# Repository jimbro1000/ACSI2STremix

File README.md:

# ACSI2STreMix

This project is based on the ACSI2STM project by Jean-Matthieu
Coulon (retro16). https://github.com/retro16/acsi2stm

## Premise and Changes

The schematics for the project are unchanged from the original
(ignoring the addition of an additional 5V connection).

The changes are primarily to the PCB layout. Bulky components have
been moved to the rear of the board to permit extra clearance 
against the ST case.

Where feasible the board dimensions have been reduced.

All 0402 SMT components have been swapped for 0603 parts to ease
the job of hand soldering. For the same reason the clearance 
between parts has been increased.

The DB19 footprint has been reimplemented to correctly align the
pins and to use individual 1mm diameter board pins (such as these: 
https://www.aliexpress.com/item/4001366384308.html). This requires 
careful alignment of the pins during assembly - I strongly 
recommend using a spare, unpopulated PCB as a jig.

The USB power connection has been moved from the right, to the
left (as viewed from the computer) to bring the connection
closer to the cartridge port for those using a SidecarT.

## Build and Programming

The build of the board should now be easier and there is no 
particular build sequence needed if you are hand soldering
the board. It is probably worth leaving the DB19 pins until
last though to avoid bending them.

The firmware for programming the STM microcontroller should
be taken from the original acsi2stm github repository, no
changes should be required as of version 5.0d (November 2024).
All of the documentation in that repository should be
applicable here too.

## Credits

Thanks to

* Jean-Matthieu for creating the ACSI2STM project
* Glenn (CRG) for prompting this with his video on building the
original retro16 version
* Lee (MFMI) for providing entertainment and support
* The rest of the board folk team for just being brilliant

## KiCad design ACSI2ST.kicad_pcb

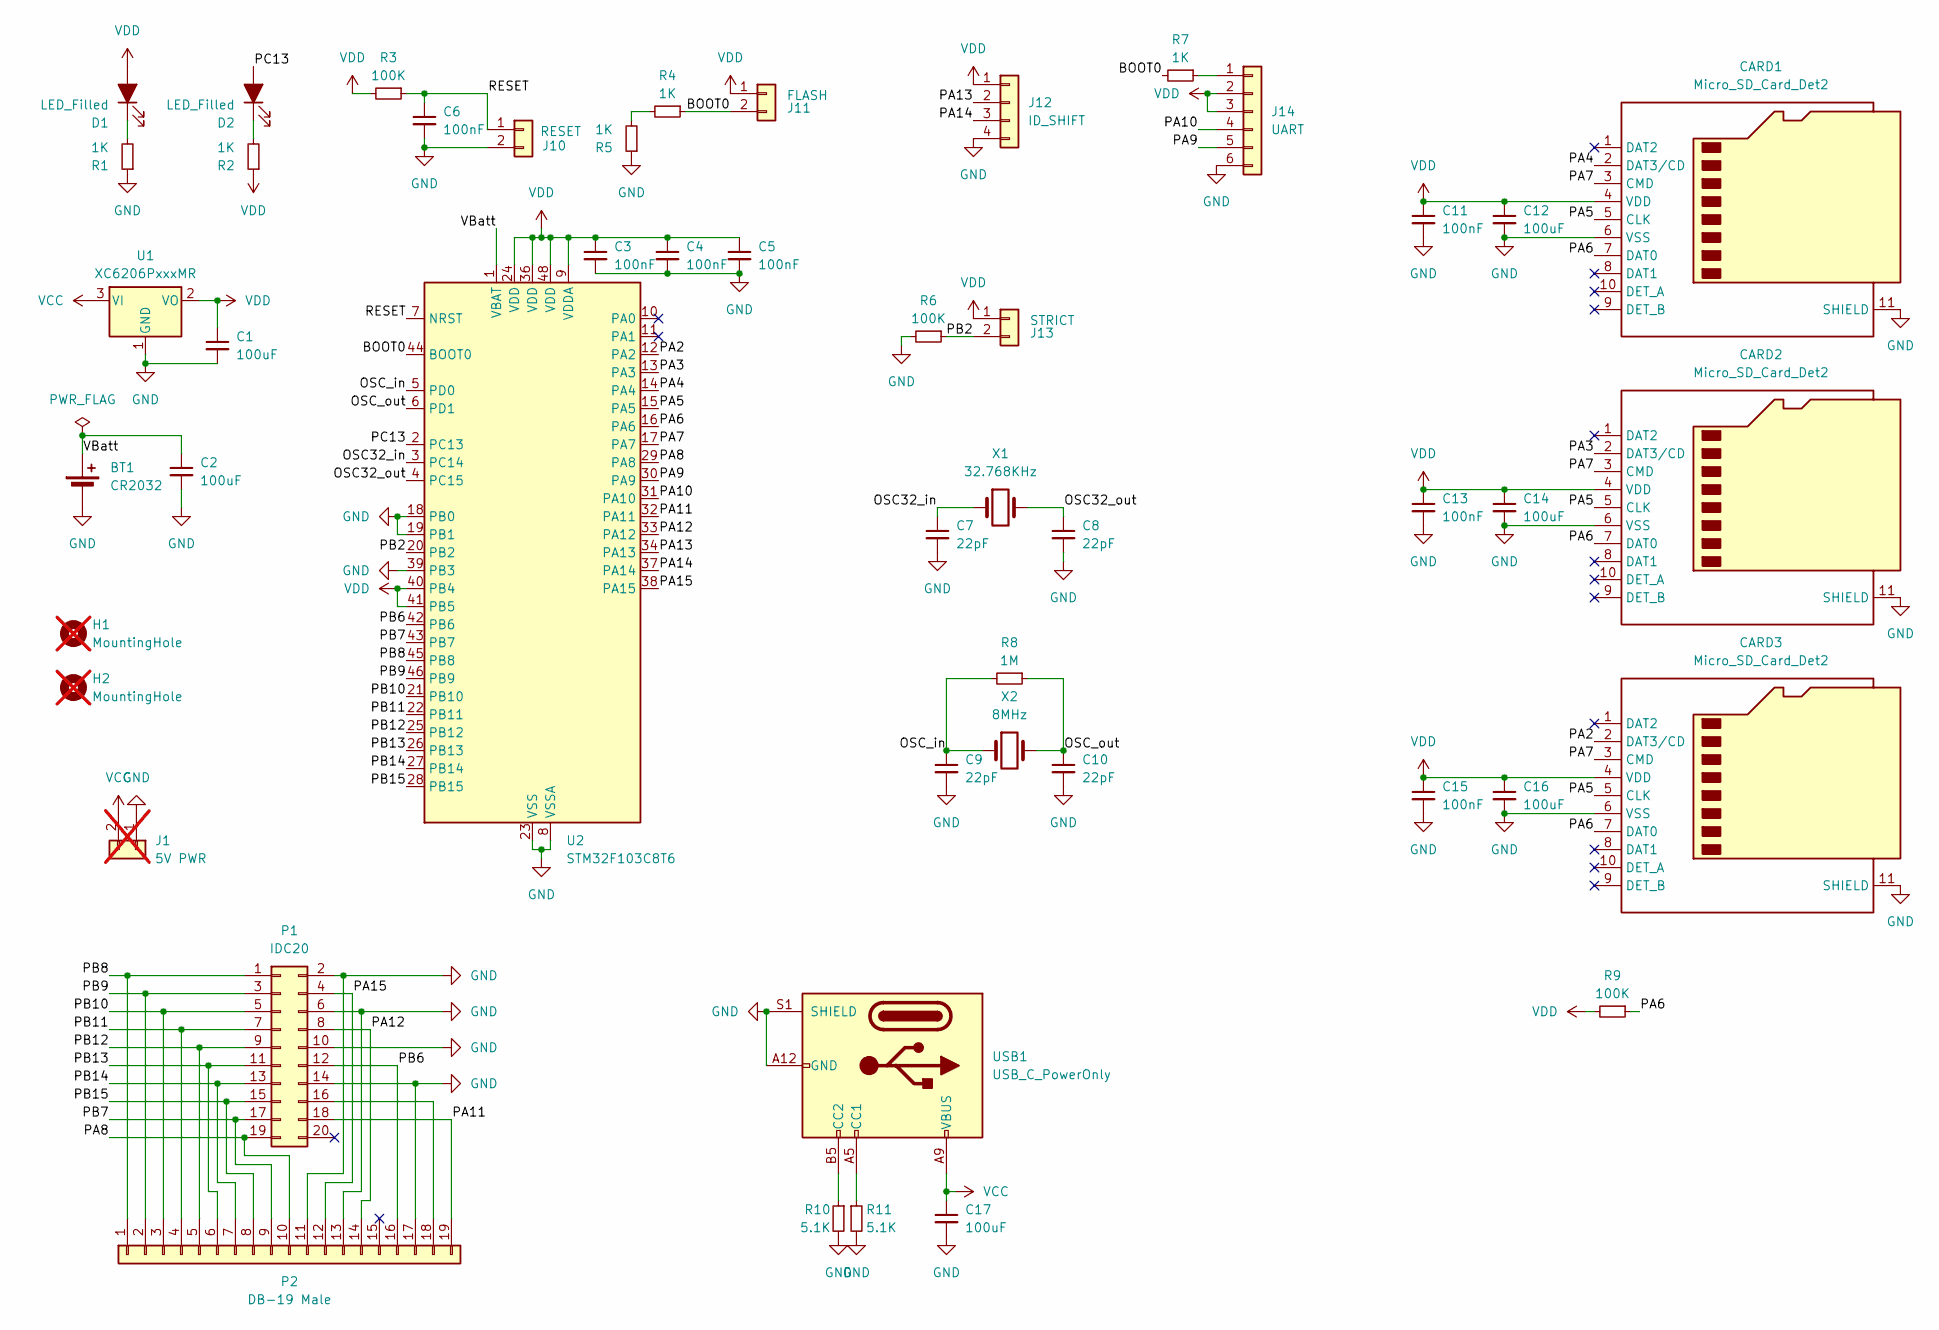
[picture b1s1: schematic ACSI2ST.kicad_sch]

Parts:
BT1: CR2032; BatteryHolder_Keystone_1060_1x2032; LCSC C238069
C1, C2, C12, C14, C16, C17: 100uF; C_1206_3216Metric; LCSC C15008
C3, C4, C5, C6, C11, C13, C15: 100nF; C_0603_1608Metric; LCSC C66501
C7, C8, C9, C10: 22pF; C_0603_1608Metric; LCSC C1653
CARD1, CARD2, CARD3: Micro_SD_Card_Det2; microSD_HC_Hirose_DM3BT-DSF-PEJS; DigiKey HR1942CT-ND
D1, D2: LED_Filled; LED_0805_2012Metric; LCSC C84256
H1, H2: MountingHole; MountingHole_2.5mm; not fitted
J1: 5V PWR; PinHeader_1x02_P2.54mm_Vertical; not fitted
J10: RESET; PinHeader_1x02_P2.54mm_Vertical; LCSC C124375
J11: FLASH; PinHeader_1x02_P2.54mm_Vertical; LCSC C124375
J12: ID_SHIFT; PinHeader_1x04_P2.54mm_Vertical; LCSC C124378
J13: STRICT; PinHeader_1x02_P2.54mm_Vertical; LCSC C124375
J14: UART; PinHeader_1x06_P2.54mm_Vertical; LCSC C40877
P1: IDC20; IDC-Header_2x10_P2.54mm_Vertical; LCSC C3405
P2: DB-19 Male; DSUB-19_Pins_Vertical
R1, R2, R4, R5, R7: 1K; R_0603_1608Metric; LCSC C2074292
R3, R6, R9: 100K; R_0603_1608Metric; LCSC C2087858
R8: 1M; R_0603_1608Metric; LCSC C2073548
R10, R11: 5.1K; R_0603_1608Metric; LCSC C1728901
U1: XC6206PxxxMR; SOT-23-3; LCSC C5446
U2: STM32F103C8T6; LQFP-48_7x7mm_P0.5mm; LCSC C8734
USB1: USB_C_PowerOnly; USB_C_Receptacle_GCT_USB4135-GF-A_6P_TopMnt_Horizontal; DigiKey 2073-USB4135-GF-ACT-ND
X1: 32.768KHz; Crystal_SMD_3215-2Pin_3.2x1.5mm; LCSC C32346
X2: 8MHz; Crystal_SMD_5032-2Pin_5.0x3.2mm; LCSC C115962

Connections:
/BOOT0: J11.2, R4.1, R7.2, U2.44 (BOOT0)
/OSC32_in: C7.1, U2.3 (PC14), X1.1
/OSC32_out: C8.1, U2.4 (PC15), X1.2
/OSC_in: C9.1, R8.2, U2.5 (PD0), X2.1
/OSC_out: C10.1, R8.1, U2.6 (PD1), X2.2
/PA2: CARD3.2 (DAT3/CD), U2.12 (PA2)
/PA3: CARD2.2 (DAT3/CD), U2.13 (PA3)
/PA4: CARD1.2 (DAT3/CD), U2.14 (PA4)
/PA5: CARD1.5 (CLK), CARD2.5 (CLK), CARD3.5 (CLK), U2.15 (PA5)
/PA6: CARD1.7 (DAT0), CARD2.7 (DAT0), CARD3.7 (DAT0), R9.1, U2.16 (PA6)
/PA7: CARD1.3 (CMD), CARD2.3 (CMD), CARD3.3 (CMD), U2.17 (PA7)
/PA8: P1.19, P2.10, U2.29 (PA8)
/PA9: J14.5, U2.30 (PA9)
/PA10: J14.4, U2.31 (PA10)
/PA11: P1.18, P2.19, U2.32 (PA11)
/PA12: P1.8, P2.14, U2.33 (PA12)
/PA13: J12.2, U2.34 (PA13)
/PA14: J12.3, U2.37 (PA14)
/PA15: P1.4, P2.12, U2.38 (PA15)
/PB2: J13.2, R6.1, U2.20 (PB2)
/PB6: P1.12, P2.16, U2.42 (PB6)
/PB7: P1.17, P2.9, U2.43 (PB7)
/PB8: P1.1, P2.1, U2.45 (PB8)
/PB9: P1.3, P2.2, U2.46 (PB9)
/PB10: P1.5, P2.3, U2.21 (PB10)
/PB11: P1.7, P2.4, U2.22 (PB11)
/PB12: P1.9, P2.5, U2.25 (PB12)
/PB13: P1.11, P2.6, U2.26 (PB13)
/PB14: P1.13, P2.7, U2.27 (PB14)
/PB15: P1.15, P2.8, U2.28 (PB15)
/PC13: D2.2 (A), U2.2 (PC13)
/RESET: C6.1, J10.1, R3.1, U2.7 (NRST)
/VBatt: BT1.1 (+), C2.1, U2.1 (VBAT)
GND: BT1.2 (-), C1.2, C2.2, C3.2, C4.2, C5.2, C6.2, C7.2, C8.2, C9.2, C10.2, C11.2, C12.2, C13.2, C14.2, C15.2, C16.2, C17.2, CARD1.6 (VSS), CARD1.11 (SHIELD), CARD2.6 (VSS), CARD2.11 (SHIELD), CARD3.6 (VSS), CARD3.11 (SHIELD), J1.1, J10.2, J12.4, J14.6, P1.2, P1.6, P1.10, P1.14, P2.11, P2.13, P2.17, R1.1, R5.1, R6.2, R10.2, R11.2, U1.1 (GND), U2.8 (VSSA), U2.18 (PB0), U2.19 (PB1), U2.23 (VSS), U2.35 (VSS), U2.39 (PB3), U2.47 (VSS), USB1.A12 (GND), USB1.B12 (GND), USB1.S1 (SHIELD)
unnamed: D1.1 (K), R1.2
unnamed: D2.1 (K), R2.2
unnamed: J14.1, R7.1
unnamed: P1.16, P2.18
unnamed: R4.2, R5.2
unnamed: R11.1, USB1.A5 (CC1)
unnamed: R10.1, USB1.B5 (CC2)
VCC: C17.1, J1.2, U1.3 (VI), USB1.A9 (VBUS), USB1.B9 (VBUS)
VDD: C1.1, C3.1, C4.1, C5.1, C11.1, C12.1, C13.1, C14.1, C15.1, C16.1, CARD1.4 (VDD), CARD2.4 (VDD), CARD3.4 (VDD), D1.2 (A), J11.1, J12.1, J13.1, J14.2, J14.3, R2.1, R3.2, R9.2, U1.2 (VO), U2.9 (VDDA), U2.24 (VDD), U2.36 (VDD), U2.40 (PB4), U2.41 (PB5), U2.48 (VDD)

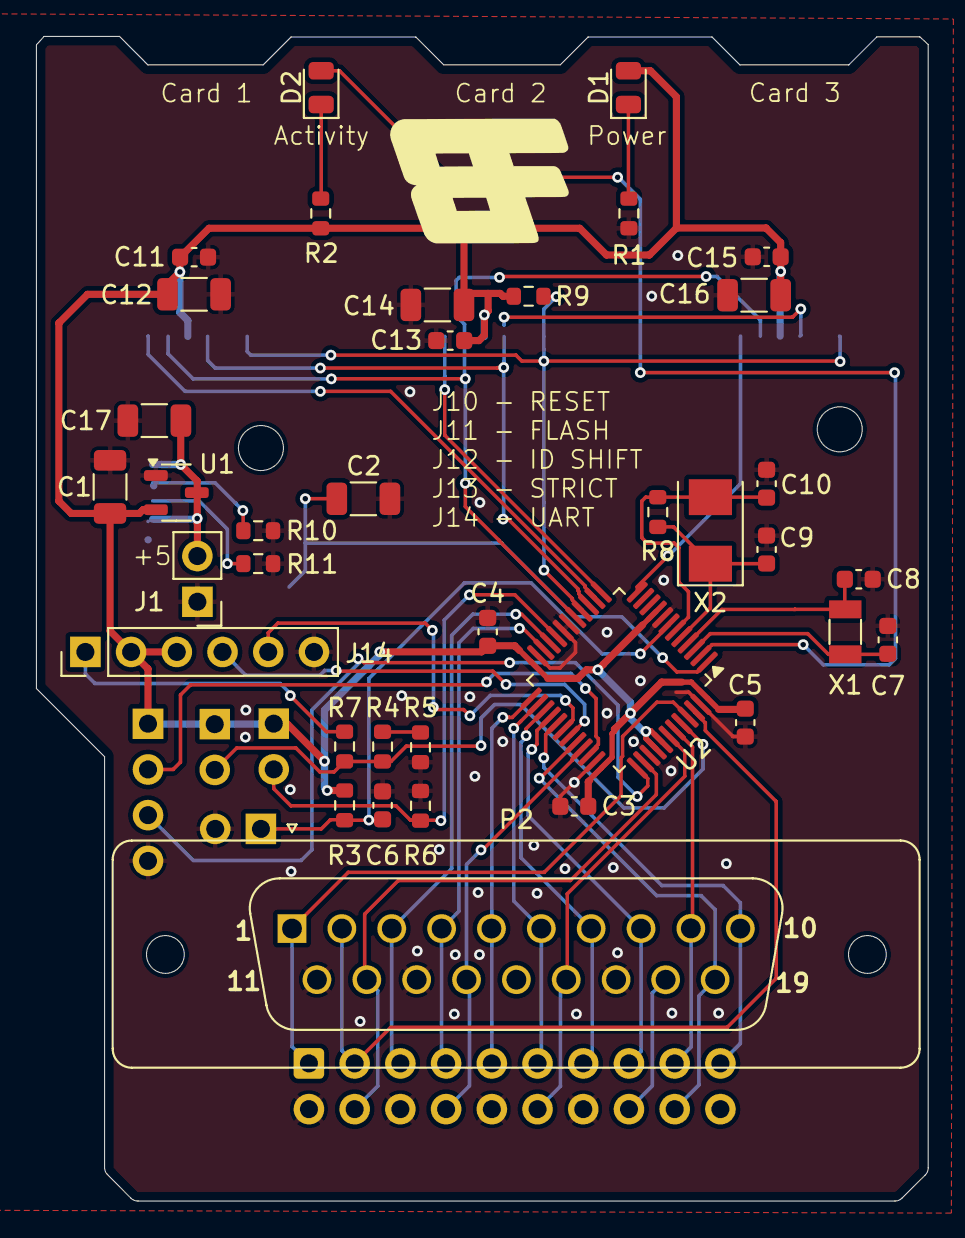
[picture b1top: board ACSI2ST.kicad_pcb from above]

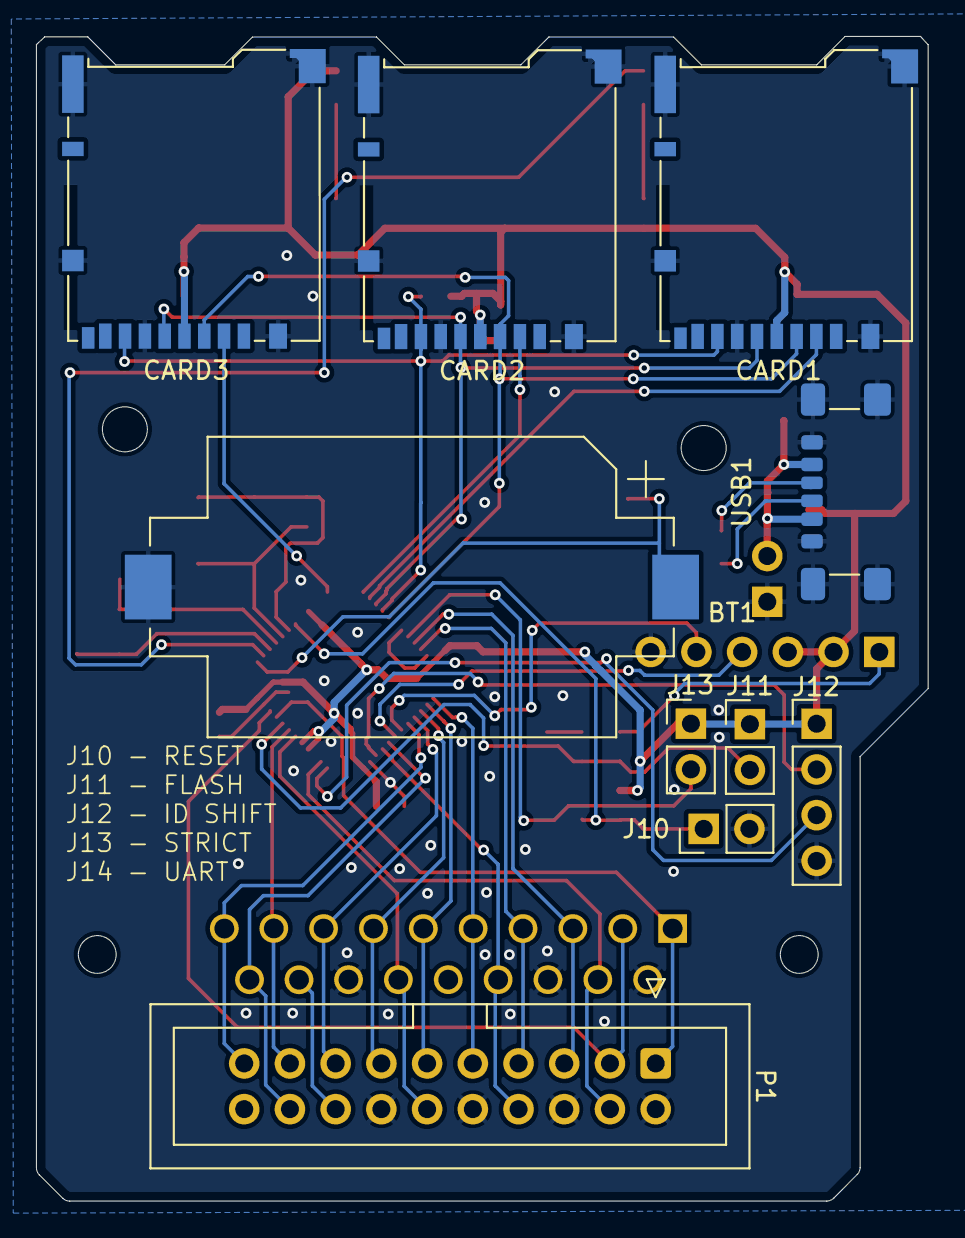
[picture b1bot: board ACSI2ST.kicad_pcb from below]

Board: 2 copper layers, 49.5 x 64.7 mm, 50 parts (10 on the bottom side), 43 nets.

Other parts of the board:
Ge: LOGO; BoardFolk

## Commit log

2025-03-13 use single pins for db19
2025-03-13 refine pcb layout
2025-03-13 fix drc violations
2025-03-14 more refinement
2025-03-16 Final update in preparation for fabrication
2025-03-16 document project
2025-03-16 tidy up
2025-03-18 add BF logo
